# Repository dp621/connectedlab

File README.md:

# Connected Lab
Monitor, log and analyze your lab equipment, process or metric

Includes software platform and example hardware devices

Software comes preconfigured with a distillation dashboard as seen below:

To Run:
- Install docker & docker-compose
- docker-compose up
- Open browser to http://localhost:3000

To simulate a short path distillation system:
- node mqtt2influx/spd_test.js

Hardware MQTT Protocol:
- Topic: 'labData'
- Data Format: {"device":"<name>", "val":<val>, "unit":"<unit>"}

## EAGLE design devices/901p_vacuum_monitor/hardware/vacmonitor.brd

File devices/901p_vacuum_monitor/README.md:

# MKS 901p loadlock transducer serial2mqtt monitor
This device reads the serial(rs-232) data stream and reports the vacuum level over wifi/mqtt as well as the onboard lcd display.

Includes the hardware design, firmware and the case design

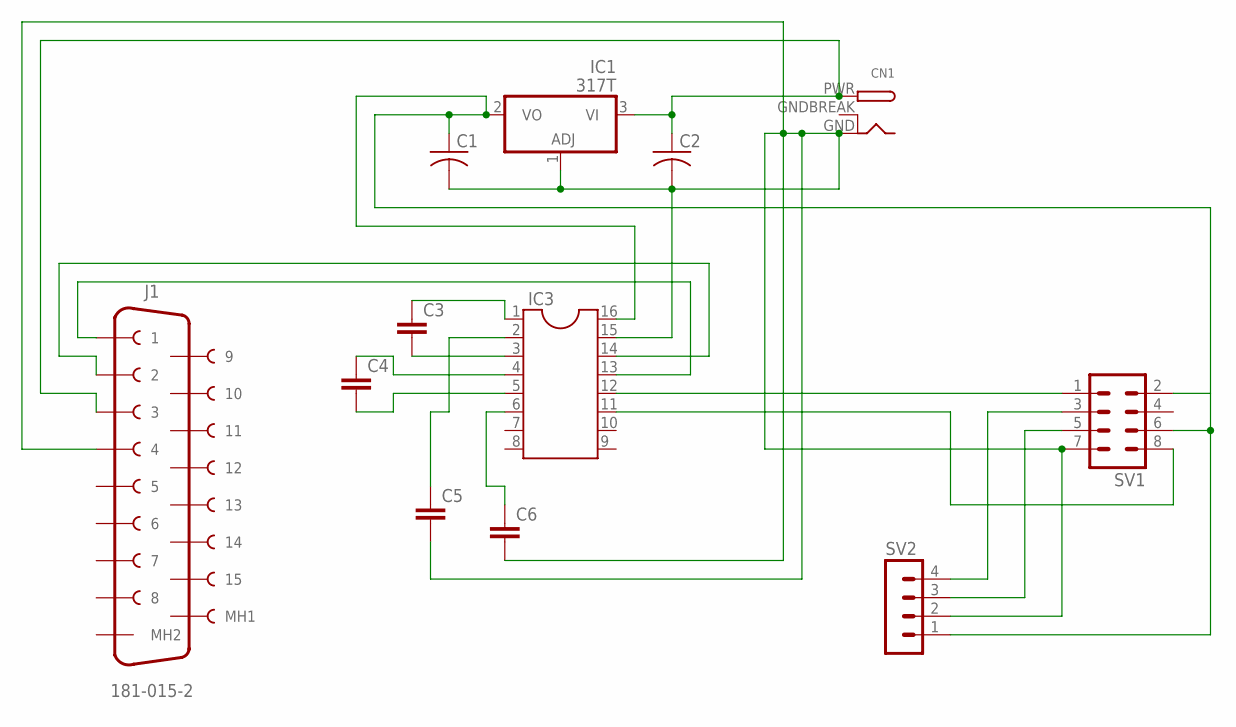
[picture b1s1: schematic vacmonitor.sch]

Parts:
C1, C2: C-US025-024X044; C025-024X044
C3, C4, C5, C6: C5/3; C5B3
CN1: DCBARRELPTH; DCJACK_2MM_PTH
IC1: 317T; TO220H
IC3: DIL16
J1: 181-015-2; 181-015-213R561
SV1: MA04-2
SV2: MA04-1

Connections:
GNDBREAK: CN1.GNDBREAK
unnamed: C2.1, CN1.PWR, IC1.3 (VI), J1.3
unnamed: IC3.11, SV1.8
unnamed: IC3.12, SV1.1
unnamed: IC3.13, J1.1
unnamed: IC3.14, J1.2
unnamed: C1.1, IC1.2 (VO), IC3.16, SV1.2, SV1.6, SV2.1
unnamed: C3.1, IC3.1
unnamed: C3.2, IC3.3
unnamed: C4.1, IC3.4
unnamed: C4.2, IC3.5
unnamed: C5.1, IC3.2
unnamed: C6.1, IC3.6
unnamed: SV1.5, SV2.3
unnamed: SV1.3, SV2.4
unnamed: C1.2, C2.2, C5.2, C6.2, CN1.GND, IC1.1 (ADJ), IC3.15, J1.4, SV1.7, SV2.2

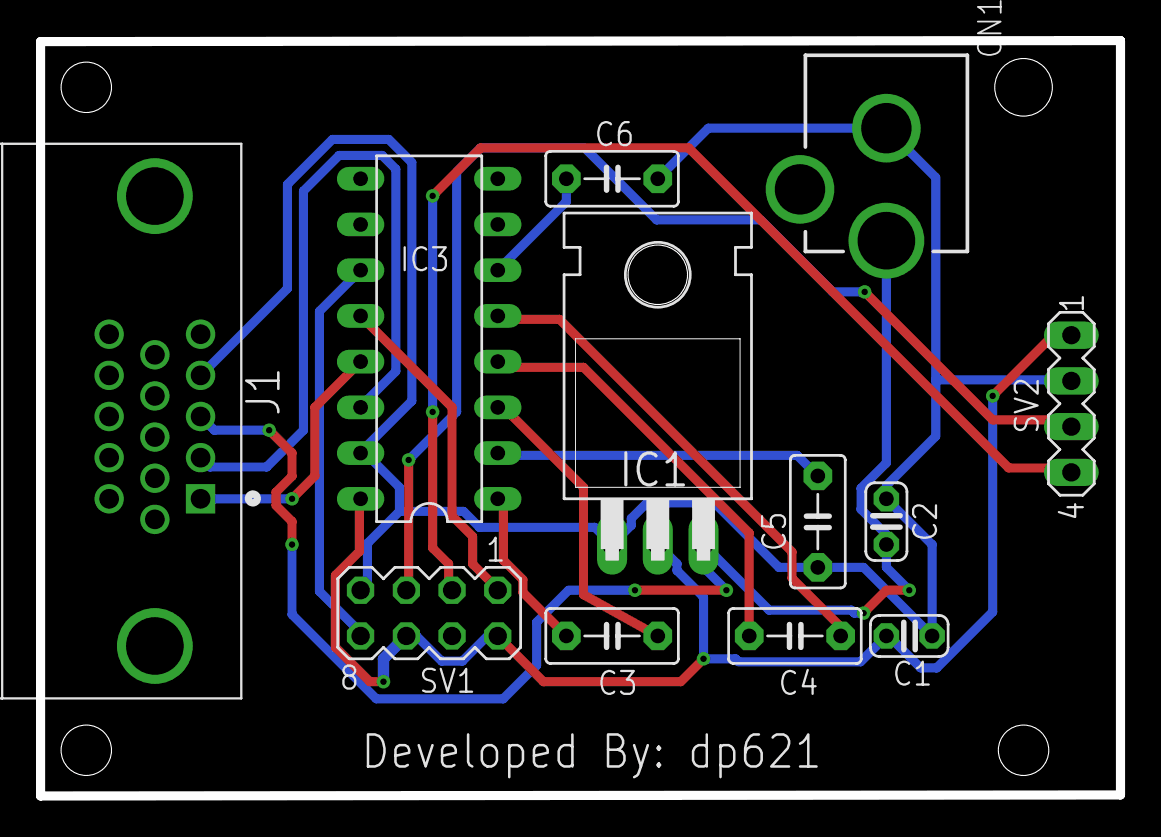
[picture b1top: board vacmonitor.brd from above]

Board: 2 copper layers, 60.0 x 42.0 mm, 12 parts (0 on the bottom side), 15 nets.

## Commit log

2022-03-28 initial upload
